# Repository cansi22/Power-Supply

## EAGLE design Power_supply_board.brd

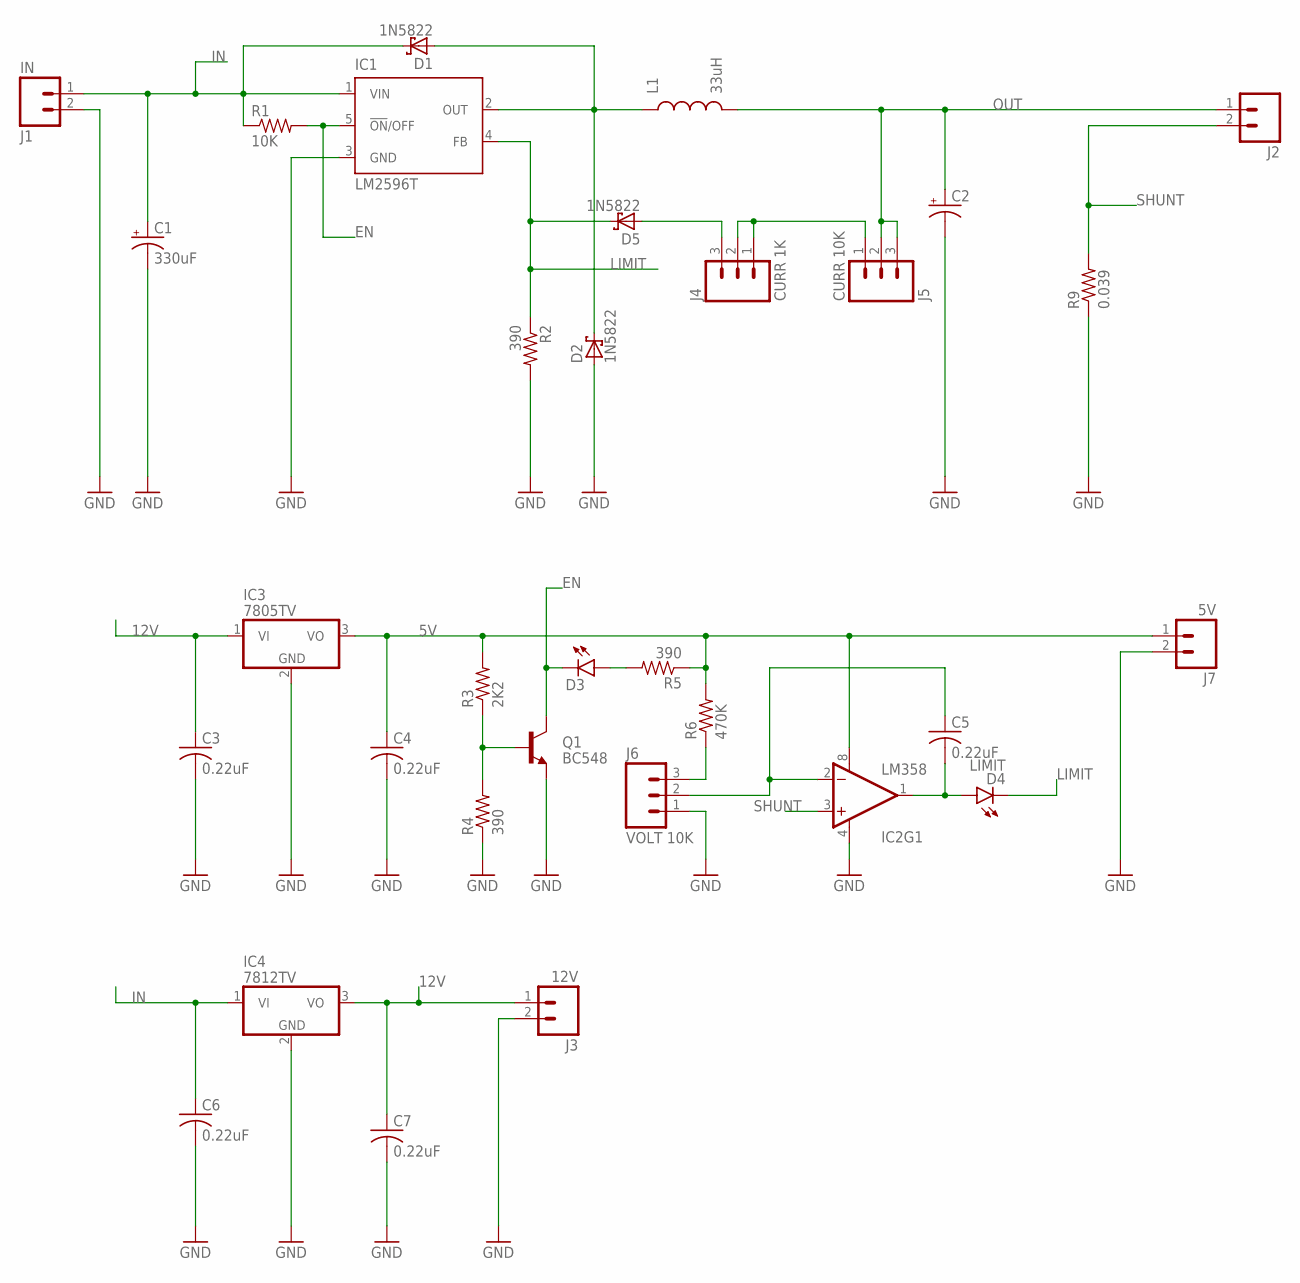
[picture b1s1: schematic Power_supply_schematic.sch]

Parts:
C1: 330uF; CPOL-RADIAL-1000UF-25V
C2: CAP_POLPTH4; CPOL-RADIAL-1000UF-25V
C3, C4, C5, C6, C7: 0.22uF; C050-025X075
D1, D2, D5: 1N5822; DO201T15
D3: LED3MM
D4: LIMIT; LED3MM
IC1: LM2596T; T05D
IC2: LM358; DIP08
IC3: 7805TV; TO220V
IC4: 7812TV; TO220V
J1: IN; SCREWTERMINAL-5MM-2
J2: M025MM; SCREWTERMINAL-5MM-2
J3: 12V; SCREWTERMINAL-5MM-2
J4: CURR 1K; MOLEX-1X3
J5: CURR 10K; MOLEX-1X3
J6: VOLT 10K; MOLEX-1X3
J7: 5V; SCREWTERMINAL-5MM-2
L1: 33uH; RLB0912
Q1: BC548; TO-92-AMMO
R1: 10K; AXIAL-0.4
R2, R4, R5: 390; AXIAL-0.4
R3: 2K2; AXIAL-0.4
R6: 470K; AXIAL-0.4
R9: 0.039; AXIAL-0.6

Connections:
5V: C4.1, IC2.8 (V+), IC3.3 (VO), J7.1, R3.P$2 (2), R5.P$1 (1), R6.P$2 (2)
12V: C3.1, C7.1, IC3.1 (VI), IC4.3 (VO), J3.1
EN: D3.K (C), IC1.5 (!ON!/OFF), Q1.1 (C), R1.P$2 (2)
GND: C1.-, C2.-, C3.2, C4.2, C6.2, C7.2, D2.A, IC1.3 (GND), IC2.4 (V-), IC3.2 (GND), IC4.2 (GND), J1.2, J3.2, J6.1, J7.2, Q1.3 (E), R2.P$2 (2), R4.P$1 (1), R9.P$1 (1)
IN: C1.+, C6.1, D1.C, IC1.1 (VIN), IC4.1 (VI), J1.1, R1.P$1 (1)
LIMIT: D4.K (C), D5.C, IC1.4 (FB), R2.P$1 (1)
unnamed: J4.1, J4.2, J5.1
unnamed: D5.A, J4.3
unnamed: D1.A, D2.C, IC1.2 (OUT), L1.1
unnamed: Q1.2 (B), R3.P$1 (1), R4.P$2 (2)
unnamed: C5.2, D4.A, IC2.1 (OUT)
unnamed: D3.A, R5.P$2 (2)
unnamed: J6.3, R6.P$1 (1)
unnamed: C5.1, IC2.2 (-IN), J6.2
OUT: C2.+, J2.1, J5.2, J5.3, L1.2
SHUNT: IC2.3 (+IN), J2.2, R9.P$2 (2)

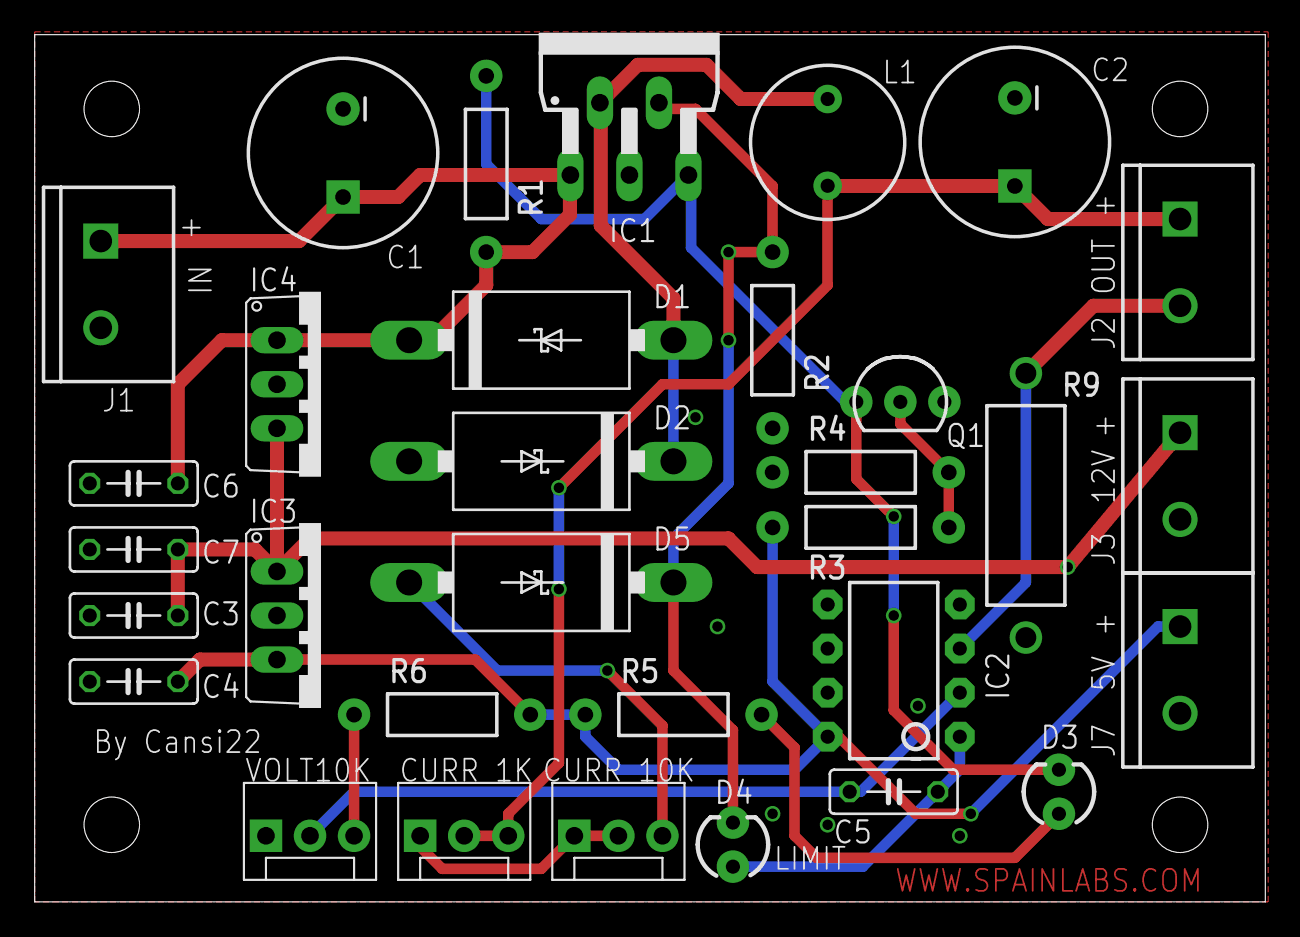
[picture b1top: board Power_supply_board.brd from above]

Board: 2 copper layers, 71.0 x 50.0 mm, 35 parts (0 on the bottom side), 16 nets.

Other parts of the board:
E$1: LOGOCANSIBOT
E$2: LOGOSLBOT
U$1: WARNINGBOT

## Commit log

2016-04-06 Regulated Power Supply 0-30V 2.5A
2016-04-06 Photos

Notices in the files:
parts and their libraries:
SparkFun-Passives: Licensing: Creative Commons ShareAlike 4.0 International - https://creativecommons.org/licenses/by-sa/4.0
